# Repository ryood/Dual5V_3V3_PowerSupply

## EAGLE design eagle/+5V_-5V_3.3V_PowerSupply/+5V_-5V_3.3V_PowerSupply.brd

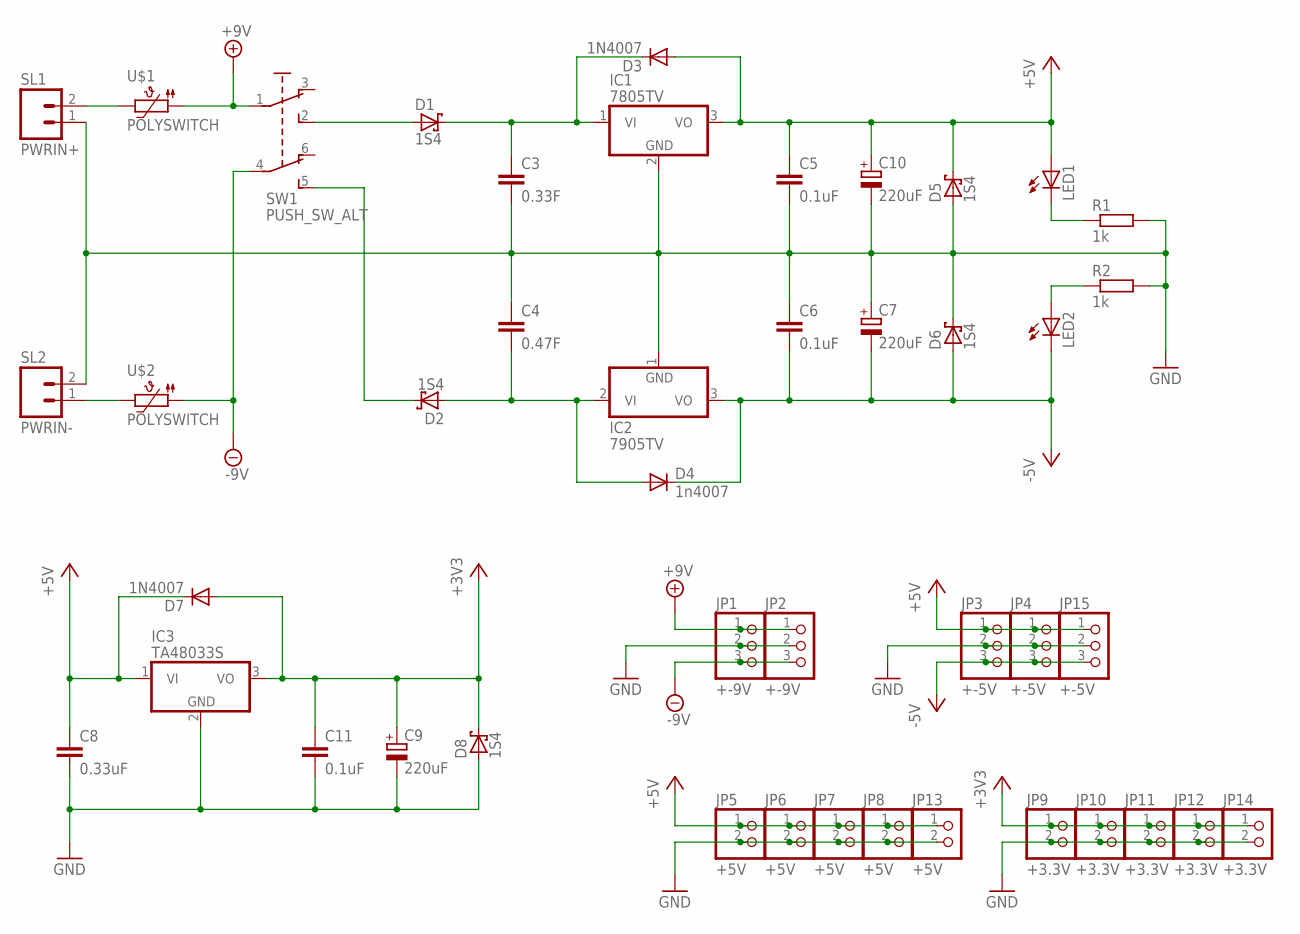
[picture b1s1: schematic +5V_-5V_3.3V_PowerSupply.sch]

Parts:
C3: 0.33F; C050-025X075
C4: 0.47F; C050-025X075
C5, C6: 0.1uF; C050-024X044
C7, C9, C10: 220uF; E2,5-6
C8: 0.33uF; C050-025X075
C11: 0.1uF; C050-025X075
D1, D2, D5, D6, D8: 1S4; DO35-7
D3, D7: 1N4007; D-7.5
D4: 1n4007; D-7.5
IC1: 7805TV; TO220V
IC2: 7905TV; TO220V
IC3: TA48033S; TO220V
JP1, JP2: +-9V; 1X03
JP3, JP4, JP15: +-5V; 1X03
JP5, JP6, JP7, JP8, JP13: +5V; 1X02
JP9, JP10, JP11, JP12, JP14: +3.3V; 1X02
LED1, LED2: LED3MM
R1, R2: 1k; 0207/7
SL1: PWRIN+; 02P
SL2: PWRIN-; 02P
SW1: PUSH_SW_ALT
U$1, U$2: POLYSWITCH

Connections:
+3V3: C9.+, C11.1, D7.A, D8.C, IC3.3 (VO), JP9.1, JP10.1, JP11.1, JP12.1, JP14.1
+5V: C5.1, C8.1, C10.+, D3.A, D5.C, D7.C, IC1.3 (VO), IC3.1 (VI), JP3.1, JP4.1, JP5.1, JP6.1, JP7.1, JP8.1, JP13.1, JP15.1, LED1.A
+9V: JP1.1, JP2.1, SW1.1, U$1.1
-5V: C6.2, C7.-, D4.C, D6.A, IC2.3 (VO), JP3.3, JP4.3, JP15.3, LED2.K (C)
-9V: JP1.3, JP2.3, SW1.4 (P1), U$2.1
GND: C3.2, C4.1, C5.2, C6.1, C7.+, C8.2, C9.-, C10.-, C11.2, D5.A, D6.C, D8.A, IC1.2 (GND), IC2.1 (GND), IC3.2 (GND), JP1.2, JP2.2, JP3.2, JP4.2, JP5.2, JP6.2, JP7.2, JP8.2, JP9.2, JP10.2, JP11.2, JP12.2, JP13.2, JP14.2, JP15.2, R1.2, R2.2, SL1.1, SL2.2
unnamed: SL2.1, U$2.2
unnamed: D1.A, SW1.2 (S)
unnamed: D2.C, SW1.5 (S1)
unnamed: C3.1, D1.C, D3.C, IC1.1 (VI)
unnamed: LED1.K (C), R1.1
unnamed: C4.2, D2.A, D4.A, IC2.2 (VI)
unnamed: LED2.A, R2.1
unnamed: SL1.2, U$1.2

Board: 2 copper layers, 44 parts (0 on the bottom side), 14 nets, no tracks yet.
